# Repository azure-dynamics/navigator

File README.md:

# Navigator

**Flight-controller Pi HAT for Azure Dynamics' Radiance ROV**

Navigator is a Raspberry Pi HAT designed to host the low-level flight controller for the Radiance ROV. It manages communication between the Raspberry Pi and the ROV's hardware, monitoring system power and routing control signals.

---

## Features

* **Flight Control:** Powered by an ESP32-S3 processor.
* **Power Management:** On-board voltage regulation supplying power directly to the Raspberry Pi and HAT logic.
* **Propulsion Signals:** Six dedicated ESC signal outputs for motor control.
* **Sensor Integration:** Includes battery voltage monitoring and I2C expansion support for added sensors (such as an IMU).
* **Mission Computer Link:** Direct hardware UART communication with the Raspberry Pi.
* **Standard Footprint:** Designed to fit the standard Raspberry Pi HAT layout with mounting holes.

---

## Board Layout & Architecture

* **Layers:** 4-layer board design.
* **Component Placement:** Most components are located on the top side, with connectors and support resistors positioned underneath.
* **Connectivity:** Features a USB-C port for programming and debugging, alongside the main Raspberry Pi GPIO header connection.

---

## Project Status

* **Schematic:** Complete (Revision 002)
* **Layout:** Waiting for review
* **Fabrication:** Not yet ordered

---

## Repository Layout

```text
navigator/
├── hardware/       KiCad project and local symbol/footprint libraries
├── fabrication/    Manufacturing outputs (BOM, Gerbers, drill files)
├── firmware/       Flight-controller code
├── docs/           Project documentation
├── LICENSE
└── README.md
```

### Local Libraries

* `hardware/library/282837-2/` — TE 282837-2 connector footprint and STEP model.
* `hardware/library/BNO086/` — BNO086 IMU symbol and footprint.
* `hardware/library/logo/` — Board logo footprint.

---

## License

Copyright (C) 2026 Azure Dynamics.

This project is licensed under the
[CERN Open Hardware Licence Version 2 - Strongly Reciprocal](LICENSE)
(`CERN-OHL-S-2.0`). See [LICENSE](LICENSE) for the full text.

Third-party symbols, footprints, and STEP models in `hardware/library/` are
included for convenience and remain subject to their original terms.

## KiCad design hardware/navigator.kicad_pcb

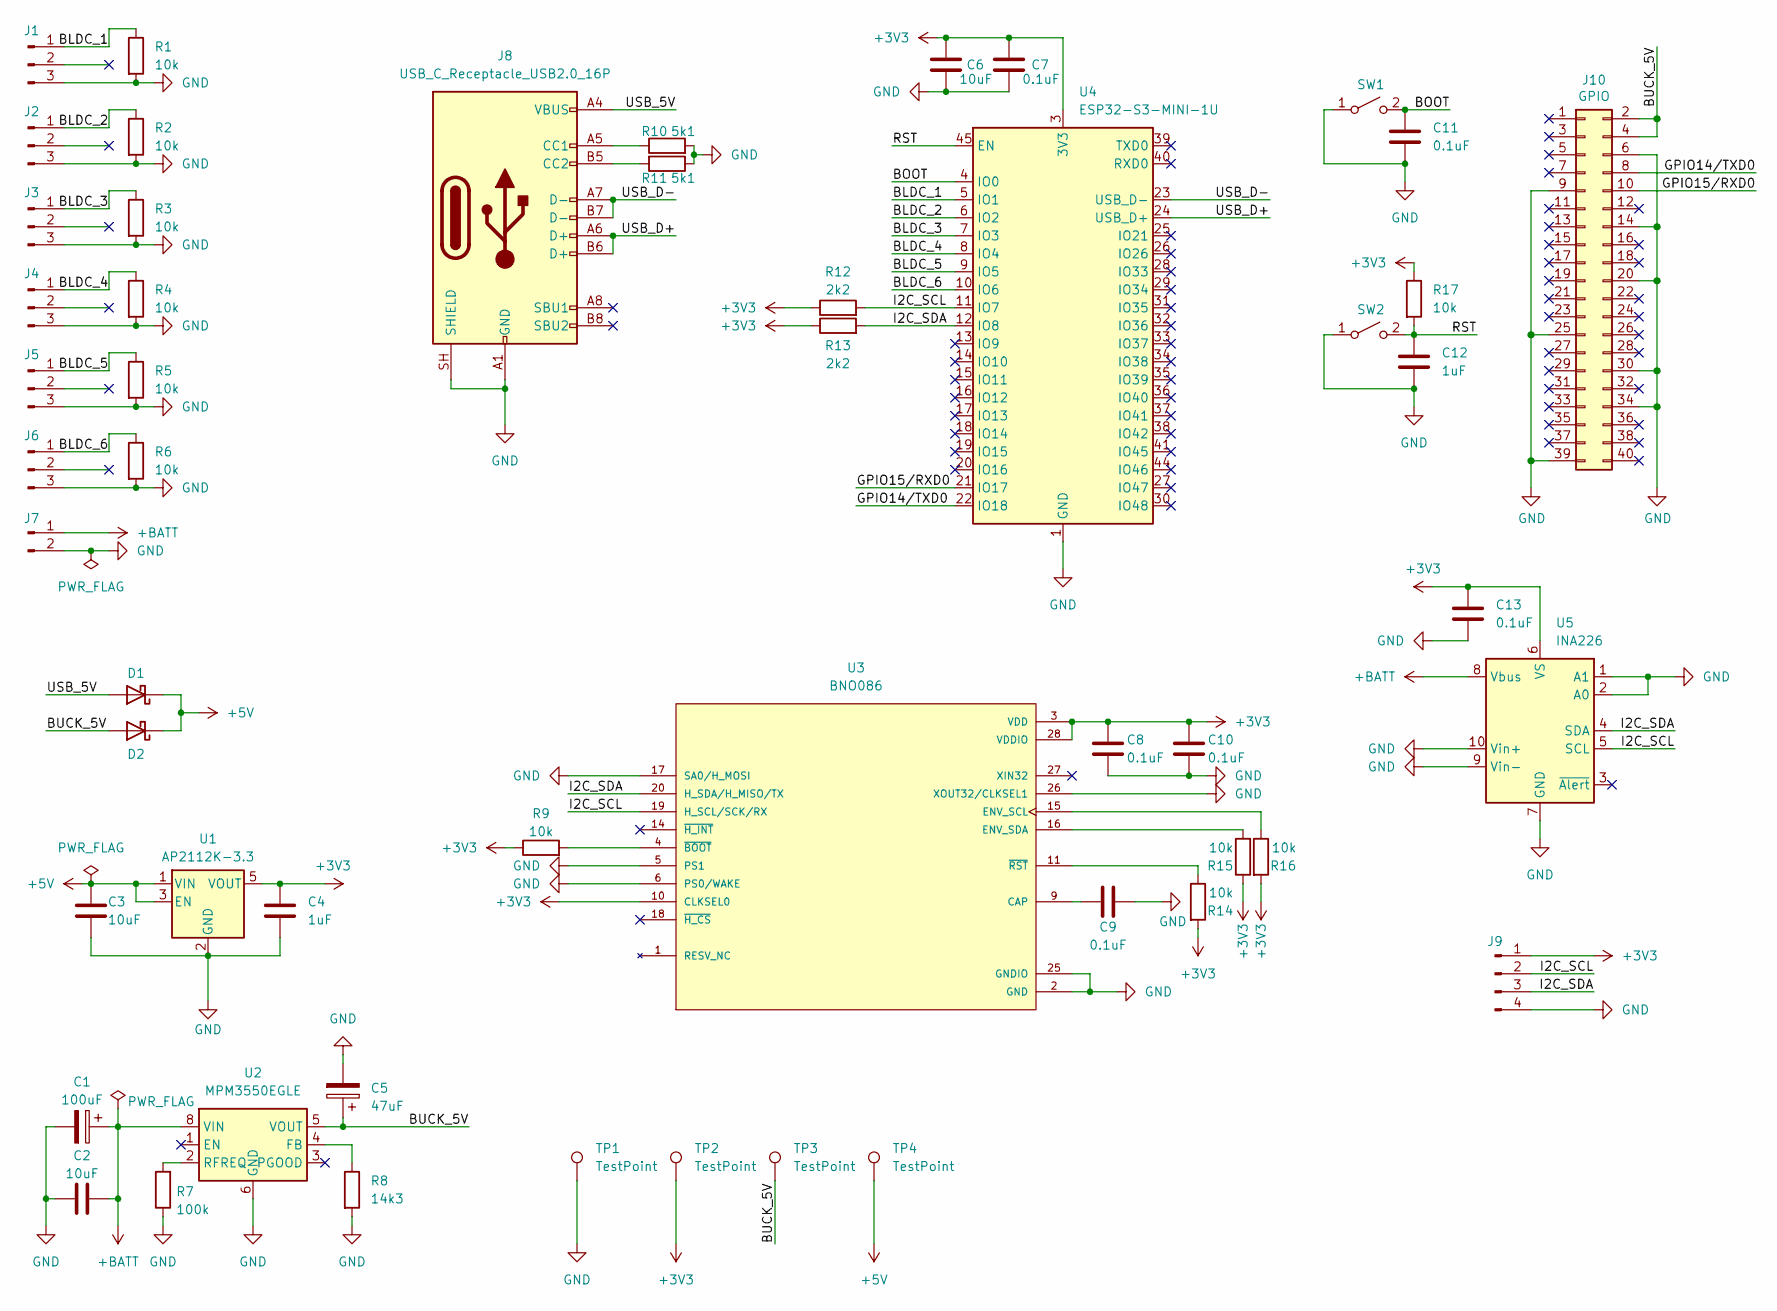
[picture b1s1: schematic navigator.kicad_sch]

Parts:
C1: 100uF; CP_Elec_8x10.5; DigiKey_PN PCE3809CT-ND
C2: 10uF; C_1210_3225Metric; DigiKey_PN 1276-3387-1-ND
C3, C6: 10uF; C_0805_2012Metric; DigiKey_PN 1276-2872-1-ND
C4, C12: 1uF; C_0805_2012Metric; DigiKey_PN 490-1695-1-ND
C5: 47uF; C_1210_3225Metric; DigiKey_PN GRM32ER61C476ME15L
C7, C8, C9, C10, C11, C13: 0.1uF; C_0805_2012Metric; DigiKey_PN 1276-1003-1-ND
D1, D2: D_Schottky; D_SOD-123; DigiKey_PN MBR0560TPMSCT-ND
J1, J2, J3, J4, J5, J6: BLDC-1; PinHeader_1x03_P2.54mm_Horizontal; DigiKey_PN 2057-PH1RB-03-UA-ND
J7: Conn_01x02_Pin; 282837-2; DigiKey_PN A113320-ND
J8: USB_C_Receptacle_USB2.0_16P; USB_C_Receptacle_Amphenol_12401948E412A; DigiKey_PN 664-12401948E412ACT-ND
J9: Conn_01x04_Pin; JST_GH_BM04B-GHS-TBT_1x04-1MP_P1.25mm_Vertical; DigiKey_PN 455-1566-1-ND
J10: GPIO; PinSocket_2x20_P2.54mm_Vertical; DigiKey_PN 1528-2831-ND
R1, R2, R3, R4, R5, R6, R9, R14, R15, R16, R17: 10k; R_0805_2012Metric; DigiKey_PN RMCF0805JT10K0CT-ND
R7: 100k; R_0805_2012Metric; DigiKey_PN 311-100KARCT-ND
R8: 14k3; R_0805_2012Metric; DigiKey_PN 118-CR0805-FX-1432ELFCT-ND
R10, R11: 5k1; R_0805_2012Metric; DigiKey_PN RMCF0805JT5K10CT-ND
R12, R13: 2k2; R_0805_2012Metric; DigiKey_PN A106060CT-ND
SW1, SW2: SW_SPST; SW_SPST_TL3305A; DigiKey_PN EG5350CT-ND
TP1, TP2, TP3, TP4: TestPoint; TestPoint_Pad_1.5x1.5mm
U1: AP2112K-3.3; SOT-23-5; DigiKey_PN AP2112K-3.3TRG1DICT-ND
U2: MPM3550EGLE; MPS_LGA-18-10EP_12x12mm_P3.3mm; DigiKey_PN 1589-2043-ND
U3: BNO086; PARTREV v1.17; DigiKey_PN 1888-BNO086CT-ND
U4: ESP32-S3-MINI-1U; DigiKey_PN 1965-ESP32-S3-MINI-1U-N8CT-ND
U5: INA226; TSSOP-10_3x3mm_P0.5mm; DigiKey_PN 296-29034-1-ND

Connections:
+3V3: C4.1, C6.1, C7.1, C8.1, C10.1, C13.1, J9.1, R9.1, R12.1, R13.1, R14.2, R15.1, R16.2, R17.1, TP2.1, U1.5 (VOUT), U3.3 (VDD), U3.10 (CLKSEL0), U3.28 (VDDIO), U4.3 (3V3), U5.6 (VS); also elsewhere on the board
+5V: C3.1, D1.1 (K), D2.1 (K), TP4.1, U1.1 (VIN), U1.3 (EN); also elsewhere on the board
+BATT: C1.1, C2.2, J7.1, U2.8 (VIN), U5.8 (Vbus)
/BLDC_1: J1.1, R1.1, U4.5 (IO1)
/BLDC_2: J2.1, R2.1, U4.6 (IO2)
/BLDC_3: J3.1, R3.1, U4.7 (IO3)
/BLDC_4: J4.1, R4.1, U4.8 (IO4)
/BLDC_5: J5.1, R5.1, U4.9 (IO5)
/BLDC_6: J6.1, R6.1, U4.10 (IO6)
/BOOT: C11.1, SW1.2 (B), U4.4 (IO0)
/BUCK_5V: C5.1, D2.2 (A), J10.2, J10.4, TP3.1, U2.5 (VOUT); also elsewhere on the board
/GPIO14/TXD0: J10.8, U4.22 (IO18)
/GPIO15/RXD0: J10.10, U4.21 (IO17)
/I2C_SCL: J9.2, R12.2, U3.19 (H_SCL/SCK/RX), U4.11 (IO7), U5.5 (SCL)
/I2C_SDA: J9.3, R13.2, U3.20 (H_SDA/H_MISO/TX), U4.12 (IO8), U5.4 (SDA)
/RST: C12.1, R17.2, SW2.2 (B), U4.45 (EN)
/USB_5V: D1.2 (A), J8.A4 (VBUS), J8.A9 (VBUS), J8.B4 (VBUS), J8.B9 (VBUS)
/USB_D+: J8.A6 (D+), J8.B6 (D+), U4.24 (USB_D+)
/USB_D-: J8.A7 (D-), J8.B7 (D-), U4.23 (USB_D-)
GND: C1.2, C2.1, C3.2, C4.2, C5.2, C6.2, C7.2, C8.2, C9.2, C10.2, C11.2, C12.2, C13.2, J1.3, J2.3, J3.3, J4.3, J5.3, J6.3, J7.2, J8.A1 (GND), J8.A12 (GND), J8.B1 (GND), J8.B12 (GND), J8.SH (SHIELD), J9.4, J10.6, J10.9, J10.14, J10.20, J10.25, J10.30, J10.34, J10.39, R1.2, R2.2, R3.2, R4.2, R5.2, R6.2, R7.1, R8.2, R10.2, R11.1, SW1.1 (A), SW2.1 (A), TP1.1, U1.2 (GND), U2.6 (GND), U2.7 (GND), U2.9 (GND), U2.10 (GND), U2.11 (GND), U2.12 (GND), U2.13 (GND), U2.14 (GND), U2.15 (GND), U2.16 (GND), U2.17 (GND), U2.18 (GND), U3.2 (GND), U3.5 (PS1), U3.6 (PS0/WAKE), U3.17 (SA0/H_MOSI), U3.25 (GNDIO), U3.26 (XOUT32/CLKSEL1), U4.1 (GND), U4.2 (GND), U4.42 (GND), U4.43 (GND), U4.46 (GND), U4.47 (GND), U4.48 (GND), U4.49 (GND), U4.50 (GND), U4.51 (GND), U4.52 (GND), U4.53 (GND), U4.54 (GND), U4.55 (GND), U4.56 (GND), U4.57 (GND), U4.58 (GND), U4.59 (GND), U4.60 (GND), U4.61 (GND), U4.62 (GND), U4.63 (GND), U4.64 (GND), U4.65 (GND), U5.1 (A1), U5.2 (A0), U5.7 (GND), U5.9 (Vin-), U5.10 (Vin+); also elsewhere on the board
unnamed: J8.A5 (CC1), R10.1
unnamed: J8.B5 (CC2), R11.2
unnamed: R8.1, U2.4 (FB)
unnamed: R7.2, U2.2 (RFREQ)
unnamed: C9.1, U3.9 (CAP)
unnamed: R16.1, U3.15 (ENV_SCL)
unnamed: R15.2, U3.16 (ENV_SDA)
unnamed: R9.2, U3.4 (~BOOT)
unnamed: R14.1, U3.11 (~RST)

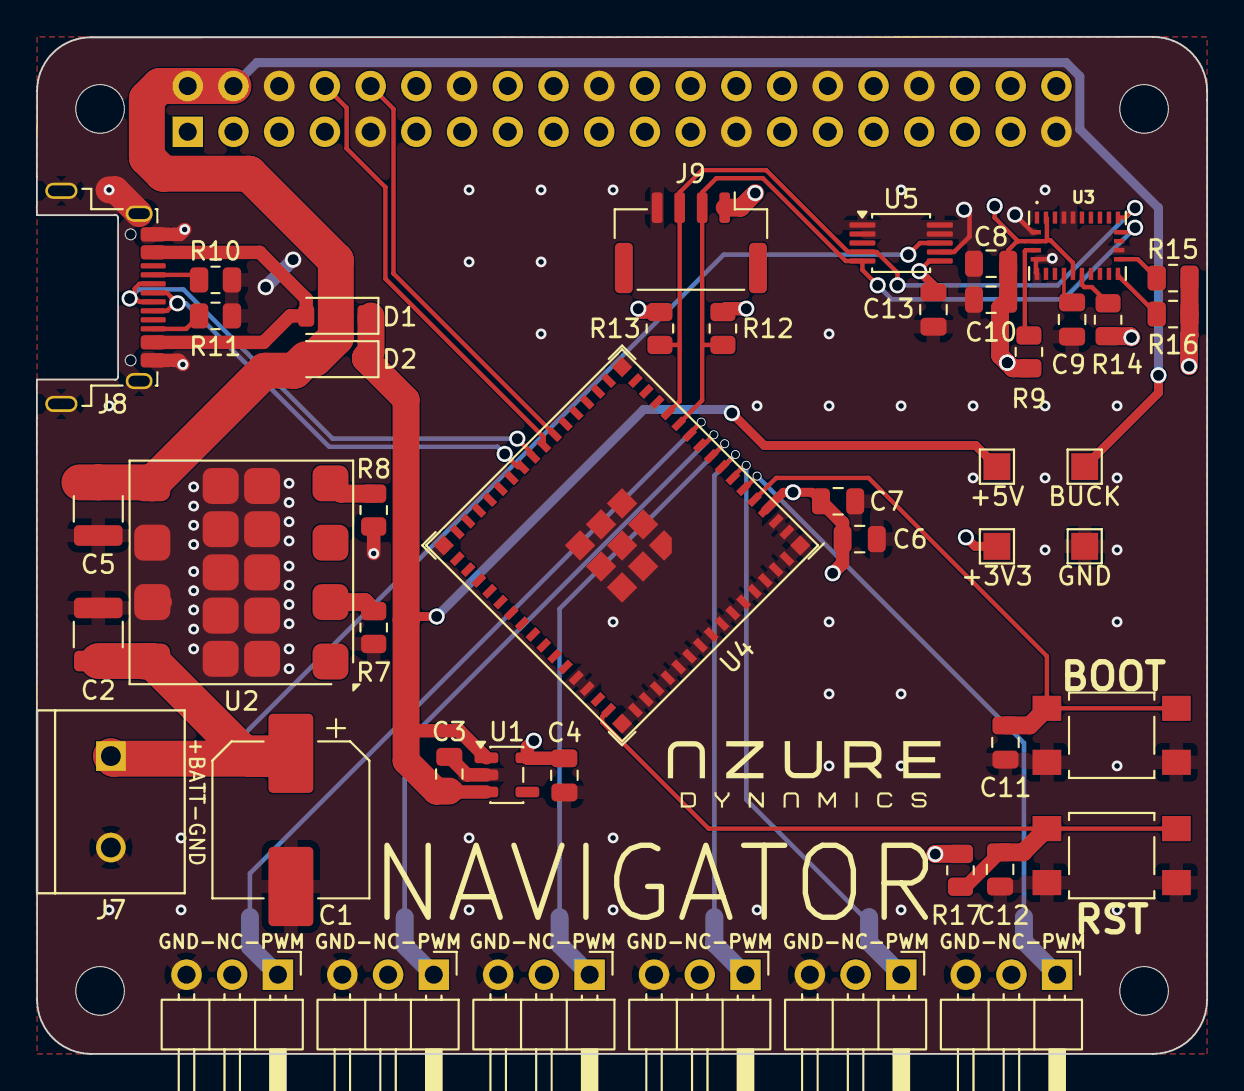
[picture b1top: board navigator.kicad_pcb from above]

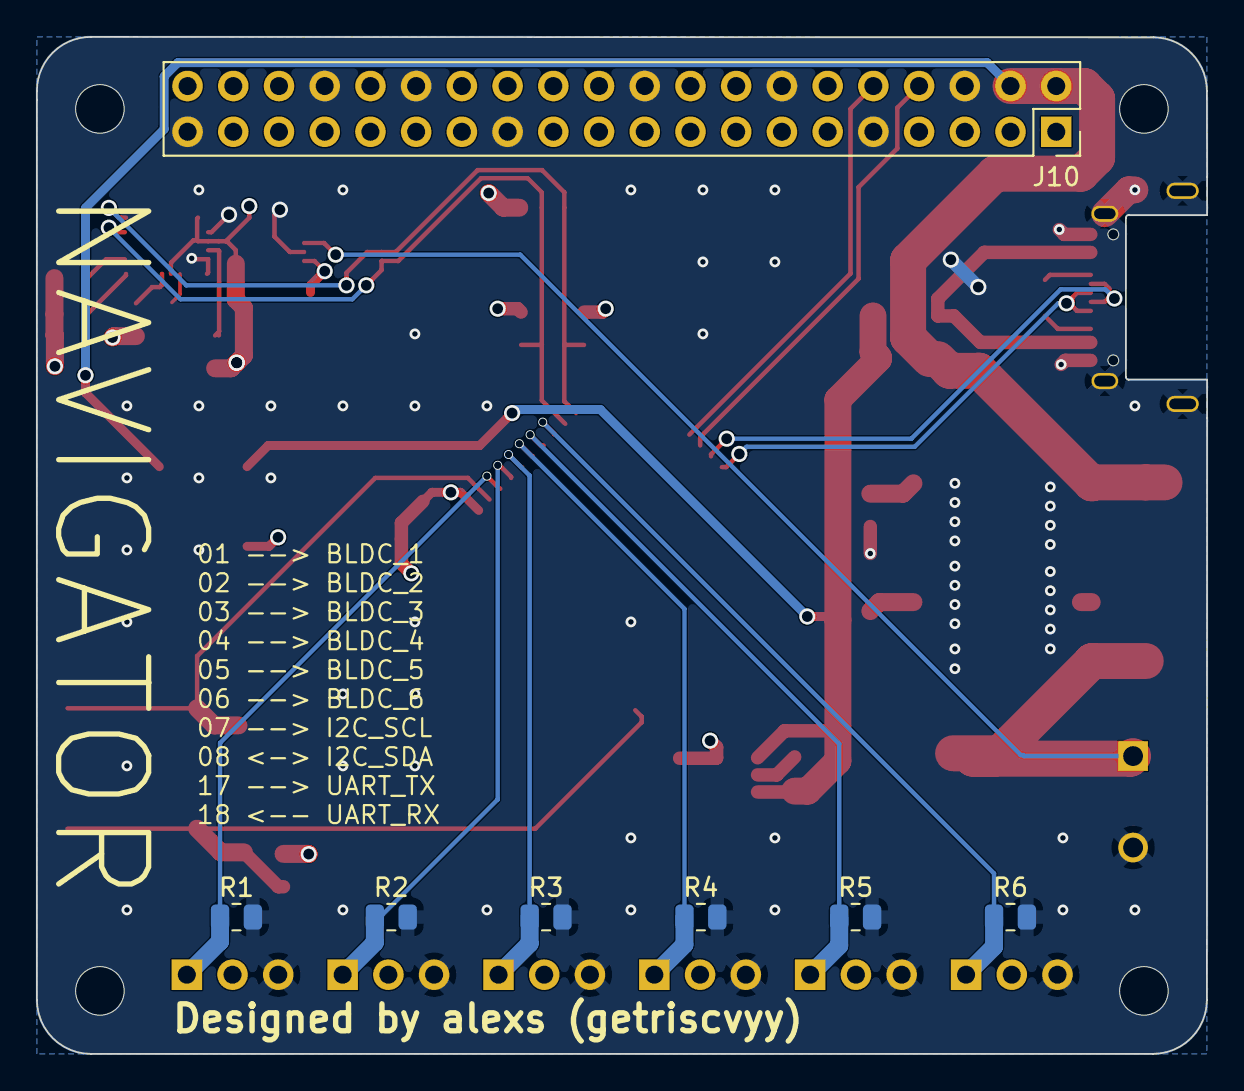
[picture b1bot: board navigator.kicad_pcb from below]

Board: 4 copper layers, 65.0 x 56.5 mm, 57 parts (7 on the bottom side), 29 nets.

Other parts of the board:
+3V3, +5V: TestPoint; TestPoint_Pad_1.5x1.5mm
BUCK: TestPoint; TestPoint_Pad_1.5x1.5mm
GND: TestPoint; TestPoint_Pad_1.5x1.5mm
MH1, MH2, MH3, MH4: MountingHole_2.7mm_M2.5

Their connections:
+3V3: +3V3.1 (1_1); also elsewhere on the board
+5V: +5V.1 (1_1); also elsewhere on the board
/BUCK_5V: BUCK.1 (1_1); also elsewhere on the board
GND: GND.1 (1_1); also elsewhere on the board
